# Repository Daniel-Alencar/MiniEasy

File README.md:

# Altímetro de dois eventos — classe EasyMini

Esquemático KiCad 10 de um altímetro barométrico de recuperação dupla (apogeu +
principal), equivalente em função ao Altus Metrum EasyMini: sensor barométrico,
registro de voo em flash, dois canais pirotécnicos com teste de continuidade,
download por USB. Sem GPS, sem acelerômetro, sem telemetria.

> **Defeito crítico em aberto:** `FIRE_B` está no PA9, que o bootloader da ROM
> leva a nível alto — o canal principal dispara se a placa entrar no bootloader
> (JP1 fechado ou flash vazia) com bateria e ignitor ligados. Até corrigir,
> grave firmware só com USB, sem bateria. Detalhes em [SINAIS.md](SINAIS.md).

Documentos:

- [SINAIS.md](SINAIS.md) — cada sinal: função, conexões, tensões, notas de firmware.
- [ALIMENTACAO.md](ALIMENTACAO.md) — por que o bloco de alimentação é assim: o "OU"
  de diodos, a escolha do regulador, o reservatório de disparo e o desacoplamento.

Arquivos:

| arquivo | conteúdo |
|---|---|
| `altimetro.kicad_sch` | esquemático, folha única A2, formato nativo KiCad 10 |
| `altimetro.kicad_pro` | projeto (inclui netclass `PIRO` de 1,0 mm) |
| `altimetro.kicad_pcb` | placa de 2 camadas, 66 × 26 mm, roteada |
| `altimetro.kicad_dru` | regra de DRC do USB que avança sobre a borda |
| `altimetro.pdf` | plotagem do esquemático |
| `fabricacao/` | Gerber + furação (zip), posição SMD, BOM, desenho de montagem, renders |
| `bom.csv` | lista de materiais exportada pelo KiCad, 54 componentes |
| `gerador/` | scripts que geram e verificam o esquemático |

## Arquitetura

```
J1 ──┬── C1 100µF ──────────────────► VBAT ──┬── J4 pino 1 (piro apogeu)
BAT  │   (reservatório de disparo)           └── J5 pino 1 (piro principal)
4-16V└── D1 ─┐
             ├─ VSYS ── U1 MCP1703 ── +3V3 ── MCU, baro, flash, buzzer
J3 USB ── D2 ┘         (SOT-89)
   └── U5 USBLC6 ── D+/D- ── U2 STM32F042K6T6 ──┬── SPI1 ──┬── U3 MS5607 (baro)
                                                │          └── U4 W25Q16 (flash)
                                                ├── ADC ───── continuidade A/B + VBAT
                                                ├── GPIO ──── Q1/Q2 AO3400A (disparo)
                                                └── TIM3 ──── Q3 + LS1 (buzzer)
```

Sete blocos no esquemático, numerados na folha: alimentação, MCU, barômetro +
memória, USB, canal A, canal B, aviso sonoro.

## Mapa de pinos do STM32F042K6T6 (LQFP32)

| pino | função | net | uso |
|---|---|---|---|
| 1, 5, 17 | VDD, VDDA, VDDIO2 | `+3V3` | C6/C9/C7 = 100 n, C8/C10 = 1 µF |
| 16, 32 | VSS, VSSA | `GND` | |
| 4 | NRST | `NRST` | C11 100 n + J2 pino 4 |
| 6 | PA0 / ADC_IN0 | `SNS_A` | continuidade canal apogeu |
| 7 | PA1 / ADC_IN1 | `SNS_B` | continuidade canal principal |
| 8 | PA2 / ADC_IN2 | `VB_SNS` | tensão de bateria (÷11) |
| 9 | PA3 | `CS_FLSH` | chip select da flash |
| 10 | PA4 | `CS_BARO` | chip select do barômetro |
| 11, 12, 13 | PA5/6/7 = SPI1 SCK/MISO/MOSI | `SCK` `MISO` `MOSI` | AF0 |
| 14 | PB0 / ADC_IN8 | `VU_SNS` | detecção de VBUS (÷2) |
| 15 | PB1 / TIM3_CH4 | `BEEP` | geração de tom |
| 18 | PA8 | `FIRE_A` | disparo apogeu |
| 19 | PA9 | `FIRE_B` | disparo principal |
| 21, 22 | PA11, PA12 | `USB_DM` `USB_DP` | USB FS device |
| 23, 24 | PA13, PA14 | `SWDIO` `SWCLK` | depuração |
| 25 | PA15 | `STAT` | LED de estado (dreno) |
| 31 | PB8 / BOOT0 | `BOOT0` | R3 10 k para GND + JP1 |
| 2, 3, 20, 26–30 | PF0, PF1, PA10, PB3–PB7 | — | marcados *no connect* |

Pinagens conferidas contra o datasheet: pino 17 é VDDIO2 e pino 16 é VSS (ST
STM32F042x4/x6); MS5607-02BA03 pino 4 = CSB e pino 5 = conexão interna, ambos no
mesmo net (datasheet TE, seção *Pin Configuration*). Atenção ao MCP1703: a
numeração muda com o encapsulamento — em SOT-89 é 1 = GND, 2 = VIN, 3 = VOUT
(em SOT-223 o pino 1 é VIN).

## Decisões de projeto

**STM32F042K6T6.** Mesma escolha do EasyMini v3. O que importa aqui é o USB
*crystal-less*: o periférico USB roda do HSI48 corrigido pelo CRS, sincronizado
ao SOF do host. Isso elimina cristal, dois capacitores e a área deles; PF0/PF1
ficam livres. Em troca, não há base de tempo precisa — o registro de voo usa o
HSI de ±1 % como base, suficiente para taxa de amostragem mas não para
medição de tempo absoluto.

**MS5607-02BA03 em SPI.** PS em GND seleciona SPI, compartilhando o barramento
com a flash. Resolução de 20 cm e conversão de 1 ms; limite de 1200 mbar e
10 mbar cobre do nível do mar a ~30 km. Barramento compartilhado é seguro porque
as duas conversões nunca são concorrentes: o firmware lê o barômetro e só depois
grava a amostra.

**W25Q16JV (16 Mbit).** 2 MByte dão ~44 min de registro a 100 Hz com amostra de
8 bytes (800 B/s) — de 10 a 20 voos de 2–4 min sem apagar; mais se a taxa cair
depois do apogeu. `WPn` e `HOLDn` ficam em nível alto por R4/R5 (10 k), o que
desativa a proteção de escrita por hardware e a pausa. Esses pinos não chegam ao
MCU, então a flash opera só em SPI simples.

**LDO MCP1703 em SOT-89, não SOT-23.** Com 16 V na entrada e 25 mA de consumo o
regulador dissipa (16 − 3,3) × 0,025 = 0,32 W. Em SOT-23 (θ_JA ≈ 250 °C/W) isso
são 80 °C de elevação; em SOT-89 (θ_JA ≈ 140 °C/W), 45 °C. O Iq de 2 µA importa
porque a placa fica armada na bancada por horas.

**OR de fontes por Schottky (D1/D2).** Bateria e USB alimentam o 3V3 por diodos
separados. O efeito colateral é a propriedade de segurança mais importante da
placa: `VBAT` alimenta os bornes pirotécnicos *diretamente*, não passa pelos
diodos — com só o USB conectado os canais ficam sem energia. Dá para programar e
baixar dados com os ignitores ligados.

**Disparo em lado baixo com pulldown no gate.** Q1/Q2 (AO3400A, 30 V, 5,7 A,
R_DS ≈ 30 mΩ) chaveiam o lado de GND do ignitor. R9/R13 de 100 k mantêm o gate
em GND enquanto o MCU está em reset, sem firmware ou travado — um pino em
tri-state não dispara nada. R8/R12 de 100 Ω limitam o pico de corrente de gate.

**Continuidade por divisor no dreno.** R10/R11 (100 k/10 k) medem o dreno de Q1.
Com ignitor intacto o nó fica em VBAT/11 (1,45 V em 16 V, 0,36 V em 4 V); com
ignitor aberto o divisor puxa o nó para 0 V. A corrente de teste que passa pelo
ignitor é VBAT/110 k, no máximo 145 µA — três ordens de grandeza abaixo da
corrente de não-disparo típica (250 mA) de um e-match. C16/C17 de 10 n filtram o
nó do ADC.

**C1 de 100 µF.** O disparo é um curto de ~1 Ω por ~1 s; sem reservatório local
a queda em VBAT faz o MCU resetar no pior momento possível. C1 fica no borne de
bateria, no mesmo laço de corrente dos bornes pirotécnicos.

**JP1 (BOOT0).** No STM32F042, BOOT0 é multiplexado com PB8. Fechando JP1 a
placa entra no bootloader DFU da ROM e aceita firmware pelo próprio USB, sem
programador. J2 (SWD 1×5, passo 1,27 mm) fica para depuração.

## Observações sobre o desenho

As ligações são feitas por **rótulos em stubs de 2,54 mm**: cada pino tem um fio
curto com o nome do net, em vez de fios longos atravessando a folha. É legal e
sem ambiguidade — a netlist extraída da geometria é idêntica à tabela de nets do
gerador — mas é um estilo compacto, não o traçado "bonito" de um esquemático
feito à mão. Reposicionar e traçar fios de verdade nos blocos é trabalho de
edição normal no Eeschema e não altera a netlist.

D1/D2/D3 estão desenhados com o catodo à esquerda (orientação padrão do símbolo,
sem espelhamento). Os rótulos deixam o sentido claro: em D1, `VBAT` entra pelo
anodo à direita e `VSYS` sai pelo catodo à esquerda.

## Placa

66 × 26 mm, 2 camadas, FR-4 1,6 mm, montagem SMD só no topo. Dois furos M3 nas
pontas, sem cobre (não ligam a placa ao suporte). Regras compatíveis com
fabricação padrão: trilha mínima 0,15 mm, folga 0,15 mm, via 0,6/0,3 mm.

| netclass | nets | trilha | folga |
|---|---|---|---|
| `PIRO` | `VBAT`, `PYRO_A`, `PYRO_B` | 0,8 mm | 0,3 mm |
| `POWER` | `+3V3`, `VSYS`, `VBUS`, `GND` | 0,4 mm | 0,2 mm |
| Default | sinais | 0,25 mm | 0,2 mm |

Disposição: bornes na borda inferior (entrada do fio para fora), USB na borda
superior esquerda, alimentação à esquerda, MCU no centro com os desacoplamentos
colados aos pinos, flash e barômetro em cima à direita (longe do regulador),
buzzer embaixo à direita. Plano de GND nas duas faces, costurado por vias.

Decisões de layout:

- **Bornes de 3,5 mm** (Metz Connect RT06302HBWC, 10 A, 0,14–1,5 mm²) em vez dos
  de 5,08 mm: metade da área, e mesma série de parafuso.
- **Pads SMD com ligação sólida ao plano**, alívio térmico só nos passantes.
  Importa para o GND do protetor de ESD (U5) e para a fonte de Q1/Q2, por onde
  volta a corrente de disparo. O pad de GND do header SWD também é sólido: no
  passo de 1,27 mm não cabem dois raios térmicos.
- **Faixa sem vias acima de cada borne** (área de regra) para os rótulos
  `+BAT-`, `APO`, `PRI` — furo de via corta a serigrafia.
- Referências que não cabem sem cobrir pad, via ou outra peça ficam fora da
  serigrafia e aparecem no desenho de montagem (`fabricacao/altimetro-montagem.pdf`).
  O verso traz legenda completa dos bornes e a pinagem do SWD.

### Gerar a placa

```sh
FREEROUTING=/caminho/freerouting-2.4.1.jar JAVA=/caminho/java25/bin/java gerador/fazer_pcb.sh
```

Requer KiCad 10 (módulo Python `pcbnew`), Java 25+ e Freerouting 2.4.1. O script
posiciona (conectores e CIs em posição fixa; passivos pelo lugar livre mais
perto do pino que atendem), exporta DSN com as larguras por classe, autorroteia,
cria planos e costura, posiciona a serigrafia e roda o DRC com paridade de
esquemático. **Só grava no projeto se o DRC passar sem nenhuma violação.** O
Freerouting não é determinístico: cada execução dá um traçado diferente, todos
verificados pelo mesmo DRC.

### Antes de encomendar

- Rodar o DRC no GUI e olhar a placa: o roteamento é automático. Funcional e
  verificado, mas vale revisar os laços de disparo e o USB a olho.
- Para montagem na JLCPCB/PCBWay: a BOM não tem códigos de fornecedor (LCSC), e
  o arquivo de posição usa a rotação do KiCad — alguns encapsulamentos (SOT-23,
  SOT-89) precisam de correção de rotação no visualizador do fabricante.
- O buzzer puxa ~100 mA de pico do 3V3 a 4 kHz. O firmware não deve tocá-lo
  enquanto mede pressão para referência de solo.

## Notas para o layout da PCB

1. O laço de disparo (J1 → C1 → J4/J5 → Q1/Q2 → GND) carrega alguns ampères por
   ~1 s. Netclass `PIRO` já está configurada em 1,0 mm; mantenha o laço curto e
   com área pequena, e não passe sinais de ADC por dentro dele.
2. O MS5607 precisa de abertura de ventilação para a pressão ambiente e **não
   pode ser lavado** (o datasheet é explícito: usar pasta no-clean). Mantenha a
   área reservada sob o sensor livre de trilhas, conforme o pad layout da TE.
3. Separe o GND de retorno pirotécnico do GND analógico do divisor de
   continuidade, unindo-os num único ponto junto ao borne de bateria.
4. U5 (USBLC6) vai o mais próximo possível do conector USB, antes de qualquer
   outra coisa nas linhas D+/D-.
5. Reserve lugar para fixar a bateria e os fios dos ignitores: são eles que
   sofrem a aceleração, não os componentes SMD.

## Verificação

`gerador/verificar.sh` gera o esquemático a partir das bibliotecas do KiCad
instalado e só grava o resultado se tudo passar:

1. o gerador recusa pino sem net e sem *no connect*, pino em dois nets, e dois
   símbolos de alimentação no mesmo ponto;
2. `check_sch.py` reextrai a netlist da geometria do arquivo e compara com a
   tabela `NETS`;
3. `check_layout.py` procura sobreposição de símbolos e rótulos e itens fora da
   folha;
4. `kicad-cli sch upgrade` converte para o formato nativo;
5. ERC do KiCad com todas as severidades — **0 erros, 0 avisos**;
6. `netcheck.py` compara a netlist exportada pelo próprio KiCad com a tabela
   `NETS` e confere cada footprint contra o filtro de footprint do símbolo;
7. exporta `altimetro.pdf` e `bom.csv`.

## O que não está feito

- Firmware e certificação.
- Proteção contra inversão de polaridade da bateria: D1 protege só o ramo de
  3V3. Os bornes pirotécnicos estão em `VBAT` direto, então bateria invertida
  polariza Q1/Q2 pelo diodo de corpo. Se isso preocupar, um P-FET em série na
  entrada resolve, ao custo de R_DS no caminho de disparo.
- Um elemento de armamento em série (chave física ou segundo FET) nos canais
  pirotécnicos. O EasyMini também não tem, mas é o acréscimo que eu faria antes
  de tratar a placa como produto.

## Regenerar

```sh
gerador/verificar.sh                      # usa /usr/share/kicad/symbols
gerador/verificar.sh /caminho/symbols     # outra instalação
```

A tabela `NETS` em `gerador/gen_sch.py` é a fonte da verdade das ligações: o
gerador falha se algum pino ficar sem net e sem *no connect*, se um pino aparecer
em dois nets, ou se dois símbolos de alimentação caírem no mesmo ponto. Depois de
editar o esquemático à mão no Eeschema, não regenere — o gerador sobrescreve o
posicionamento.

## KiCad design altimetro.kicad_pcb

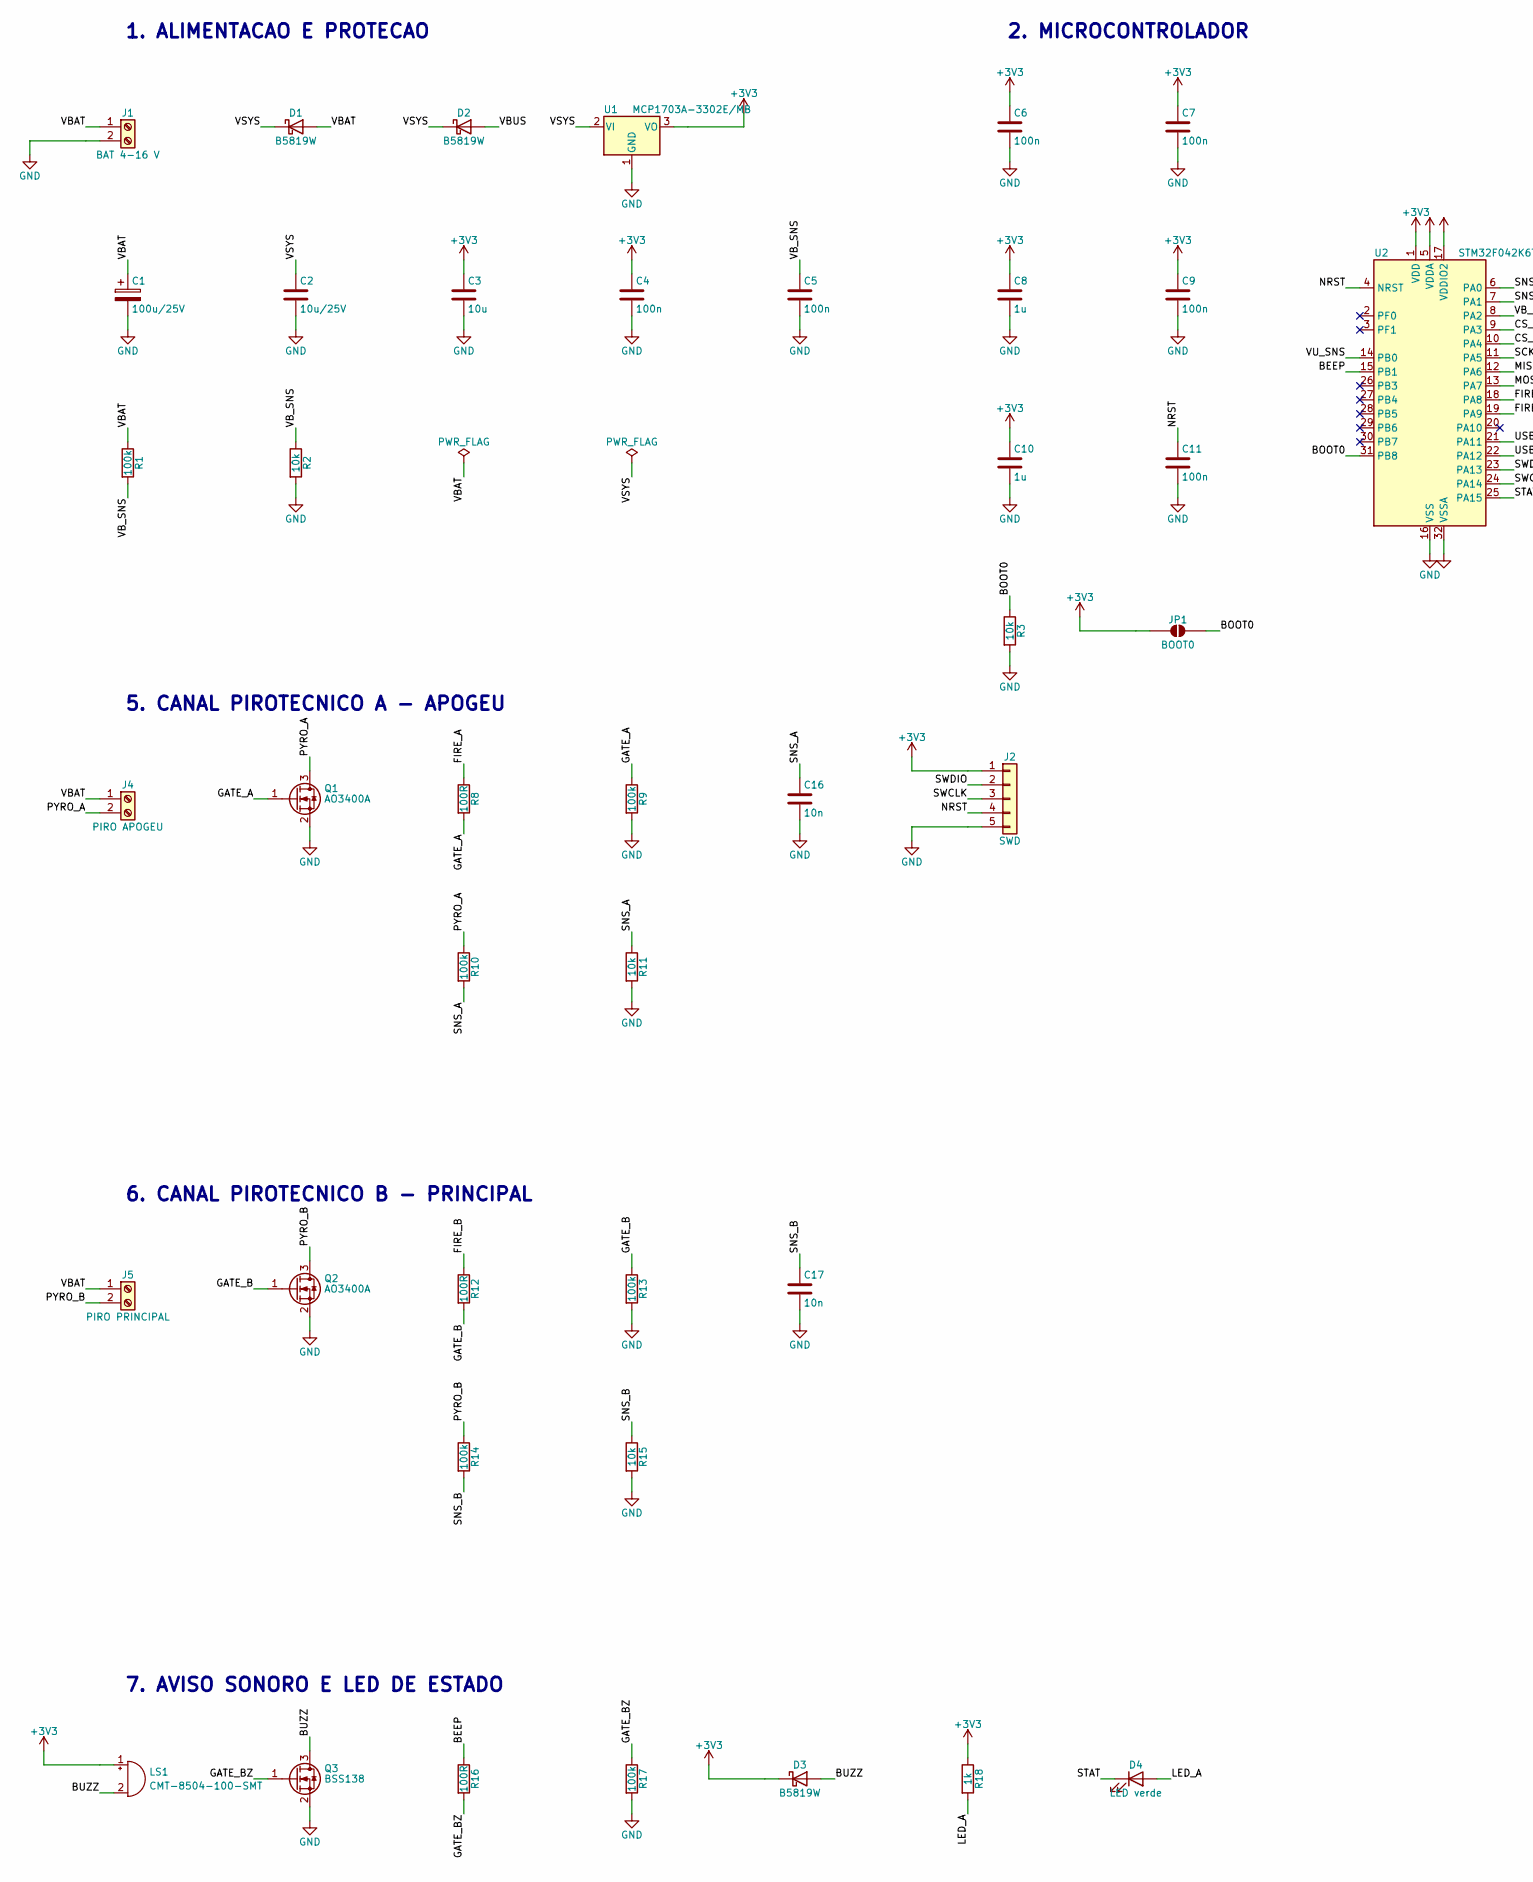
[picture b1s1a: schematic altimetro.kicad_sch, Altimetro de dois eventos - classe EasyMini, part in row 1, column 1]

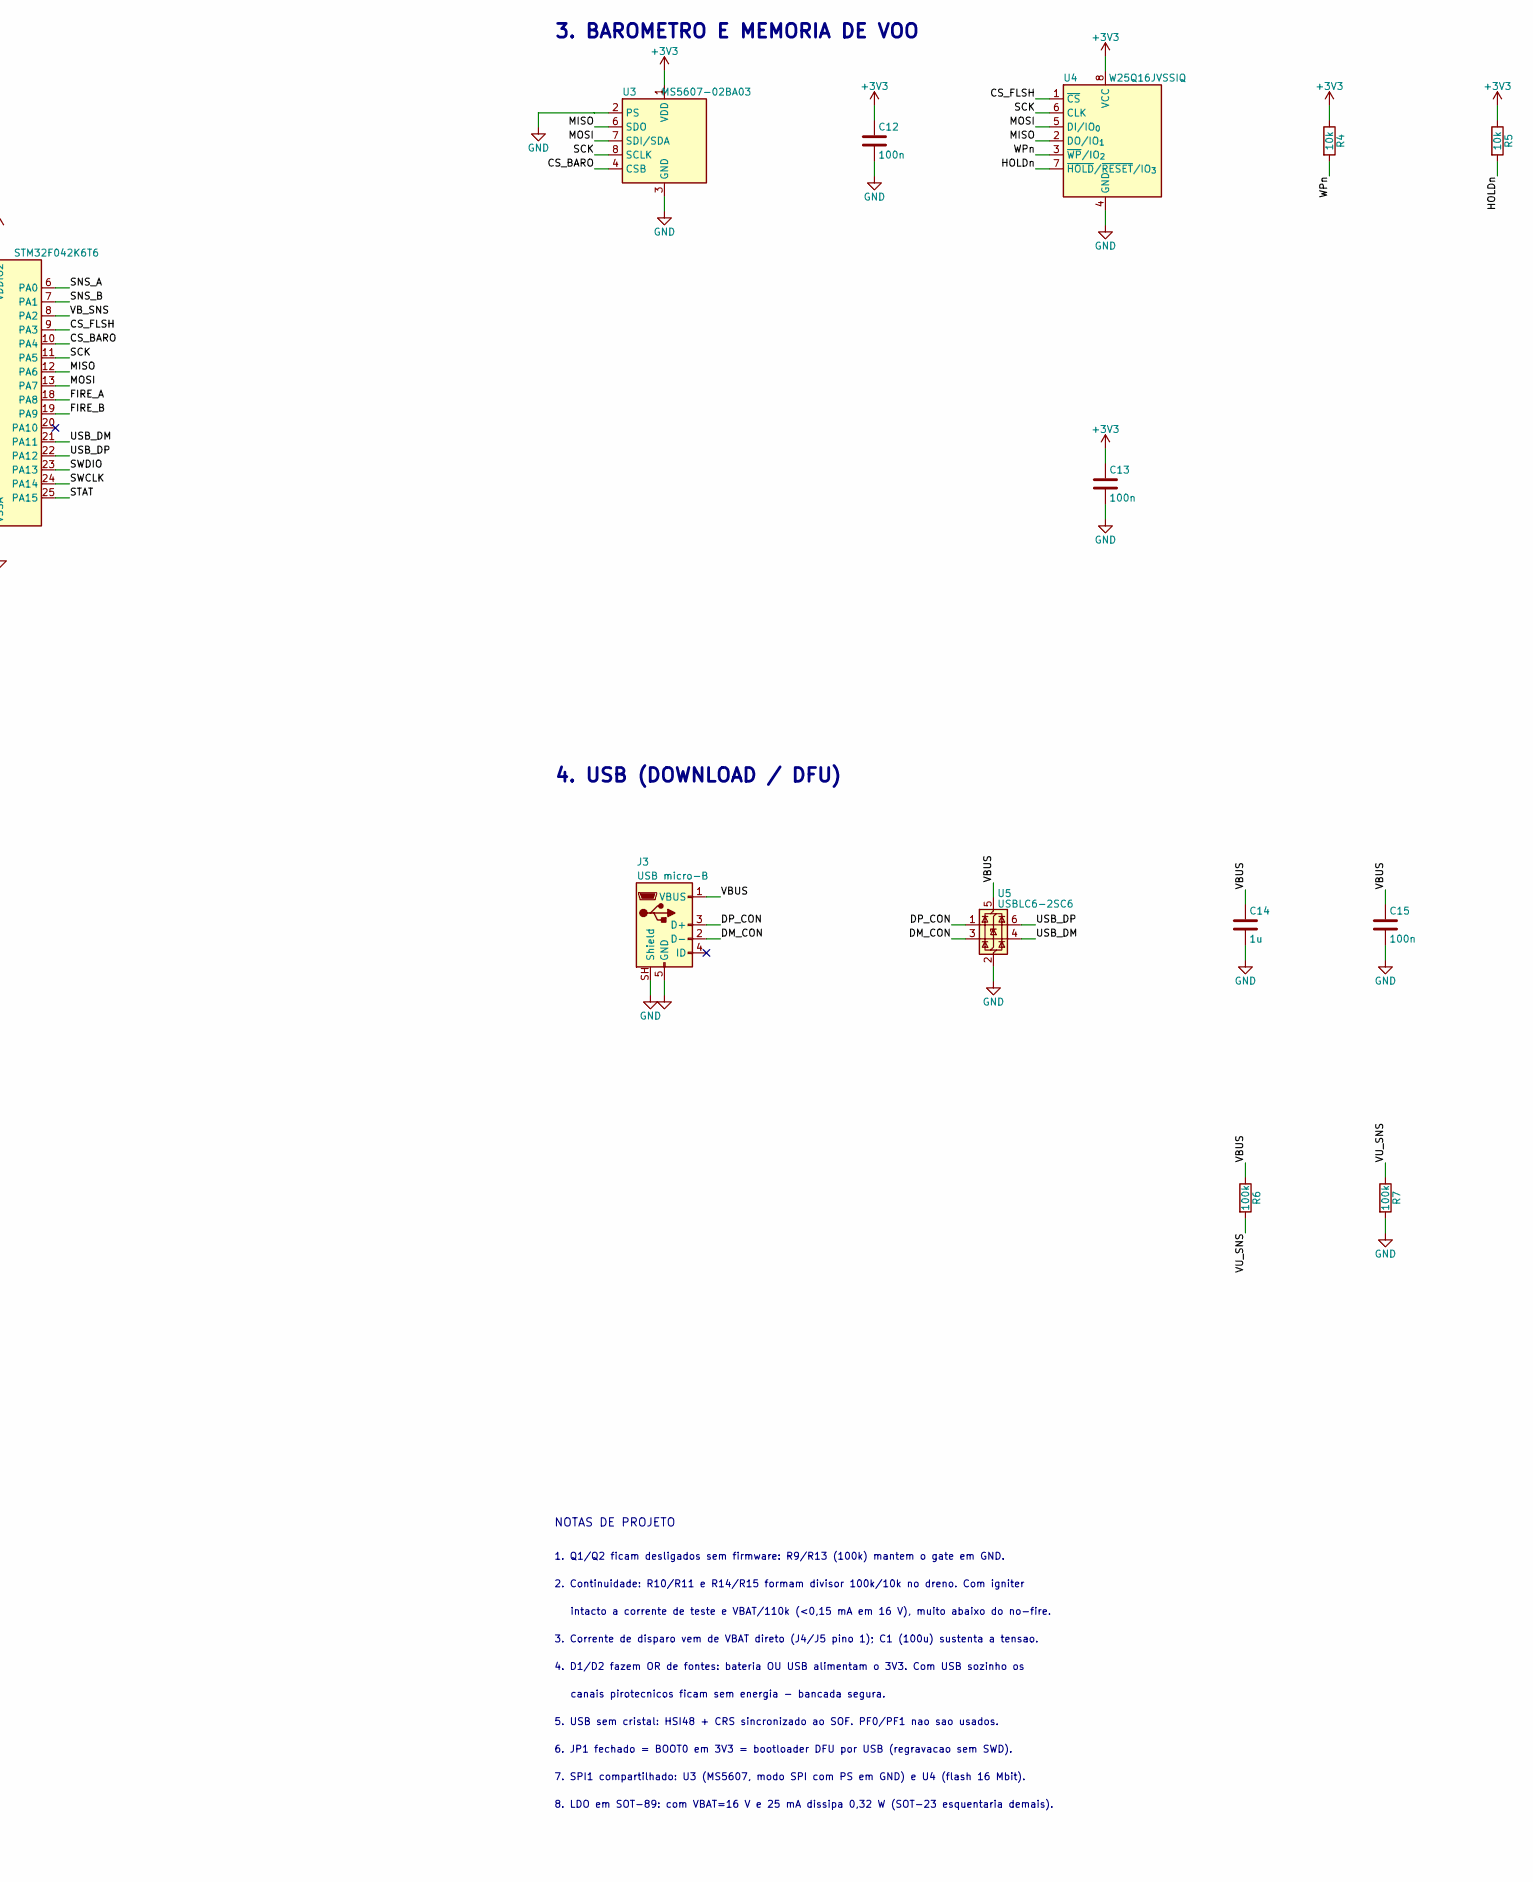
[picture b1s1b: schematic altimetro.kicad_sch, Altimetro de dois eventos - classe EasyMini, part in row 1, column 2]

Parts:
C1: 100u/25V; CP_Elec_6.3x7.7
C2: 10u/25V; C_0805_2012Metric
C3: 10u; C_0805_2012Metric
C4, C5, C6, C7, C9, C11, C12, C13, C15: 100n; C_0603_1608Metric
C8, C10, C14: 1u; C_0603_1608Metric
C16, C17: 10n; C_0603_1608Metric
D1, D2, D3: B5819W; D_SOD-123
D4: LED verde; LED_0603_1608Metric
J1: BAT 4-16 V; TerminalBlock_MetzConnect_Type059_RT06302HBWC_1x02_P3.50mm_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
J2: SWD; PinHeader_1x05_P1.27mm_Vertical
J3: USB micro-B; USB_Micro-B_Molex_47346-0001
J4: PIRO APOGEU; TerminalBlock_MetzConnect_Type059_RT06302HBWC_1x02_P3.50mm_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
J5: PIRO PRINCIPAL; TerminalBlock_MetzConnect_Type059_RT06302HBWC_1x02_P3.50mm_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
JP1: BOOT0; SolderJumper-2_P1.3mm_Open_RoundedPad1.0x1.5mm
LS1: CMT-8504-100-SMT; MagneticBuzzer_CUI_CMT-8504-100-SMT
Q1, Q2: AO3400A; SOT-23
Q3: BSS138; SOT-23
R1, R6, R7, R9, R10, R13, R14, R17: 100k; R_0603_1608Metric
R2, R3, R4, R5, R11, R15: 10k; R_0603_1608Metric
R8, R12, R16: 100R; R_0603_1608Metric
R18: 1k; R_0603_1608Metric
U1: MCP1703A-3302E/MB; SOT-89-3
U2: STM32F042K6T6; LQFP-32_7x7mm_P0.8mm
U3: MS5607-02BA03; LGA-8_3x5mm_P1.25mm
U4: W25Q16JVSSIQ; SOIC-8_5.3x5.3mm_P1.27mm
U5: USBLC6-2SC6; SOT-23-6

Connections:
+3V3: C3.1, C4.1, C6.1, C7.1, C8.1, C9.1, C10.1, C12.1, C13.1, D3.1 (K), J2.1, JP1.1 (A), LS1.1 (+), R4.1, R5.1, R18.1, U1.3 (VO), U2.1 (VDD), U2.5 (VDDA), U2.17 (VDDIO2), U3.1 (VDD), U4.8 (VCC)
/BEEP: R16.1, U2.15 (PB1)
/BOOT0: JP1.2 (B), R3.1, U2.31 (PB8)
/BUZZ: D3.2 (A), LS1.2 (-), Q3.3 (D)
/CS_BARO: U2.10 (PA4), U3.4 (CSB), U3.5 (CSB)
/CS_FLSH: U2.9 (PA3), U4.1 (~CS)
/DM_CON: J3.2 (D-), U5.3 (I/O2)
/DP_CON: J3.3 (D+), U5.1 (I/O1)
/FIRE_A: R8.1, U2.18 (PA8)
/FIRE_B: R12.1, U2.19 (PA9)
/GATE_A: Q1.1 (G), R8.2, R9.1
/GATE_B: Q2.1 (G), R12.2, R13.1
/GATE_BZ: Q3.1 (G), R16.2, R17.1
/HOLDn: R5.2, U4.7 (~HOLD/~RESET/IO_{3})
/LED_A: D4.2 (A), R18.2
/MISO: U2.12 (PA6), U3.6 (SDO), U4.2 (DO/IO_{1})
/MOSI: U2.13 (PA7), U3.7 (SDI/SDA), U4.5 (DI/IO_{0})
/NRST: C11.1, J2.4, U2.4 (NRST)
/PYRO_A: J4.2, Q1.3 (D), R10.1
/PYRO_B: J5.2, Q2.3 (D), R14.1
/SCK: U2.11 (PA5), U3.8 (SCLK), U4.6 (CLK)
/SNS_A: C16.1, R10.2, R11.1, U2.6 (PA0)
/SNS_B: C17.1, R14.2, R15.1, U2.7 (PA1)
/STAT: D4.1 (K), U2.25 (PA15)
/SWCLK: J2.3, U2.24 (PA14)
/SWDIO: J2.2, U2.23 (PA13)
/USB_DM: U2.21 (PA11), U5.4 (I/O2)
/USB_DP: U2.22 (PA12), U5.6 (I/O1)
/VBAT: C1.1, D1.2 (A), J1.1, J4.1, J5.1, R1.1
/VBUS: C14.1, C15.1, D2.2 (A), J3.1 (VBUS), R6.1, U5.5 (VBUS)
/VB_SNS: C5.1, R1.2, R2.1, U2.8 (PA2)
/VSYS: C2.1, D1.1 (K), D2.1 (K), U1.2 (VI)
/VU_SNS: R6.2, R7.1, U2.14 (PB0)
/WPn: R4.2, U4.3 (~WP/IO_{2})
GND: C1.2, C2.2, C3.2, C4.2, C5.2, C6.2, C7.2, C8.2, C9.2, C10.2, C11.2, C12.2, C13.2, C14.2, C15.2, C16.2, C17.2, J1.2, J2.5, J3.5 (GND), J3.SH (Shield), Q1.2 (S), Q2.2 (S), Q3.2 (S), R2.2, R3.2, R7.2, R9.2, R11.2, R13.2, R15.2, R17.2, U1.1 (GND), U2.16 (VSS), U2.32 (VSSA), U3.2 (PS), U3.3 (GND), U4.4 (GND), U5.2 (GND)

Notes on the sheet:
8. LDO em SOT-89: com VBAT=16 V e 25 mA dissipa 0,32 W (SOT-23 esquentaria demais).
4. D1/D2 fazem OR de fontes: bateria OU USB alimentam o 3V3. Com USB sozinho os
2. MICROCONTROLADOR
intacto a corrente de teste e VBAT/110k (<0,15 mA em 16 V), muito abaixo do no-fire.
3. BAROMETRO E MEMORIA DE VOO
1. Q1/Q2 ficam desligados sem firmware: R9/R13 (100k) mantem o gate em GND.
4. USB (DOWNLOAD / DFU)
7. SPI1 compartilhado: U3 (MS5607, modo SPI com PS em GND) e U4 (flash 16 Mbit).
6. JP1 fechado = BOOT0 em 3V3 = bootloader DFU por USB (regravacao sem SWD).
3. Corrente de disparo vem de VBAT direto (J4/J5 pino 1); C1 (100u) sustenta a tensao.
2. Continuidade: R10/R11 e R14/R15 formam divisor 100k/10k no dreno. Com igniter
NOTAS DE PROJETO
canais pirotecnicos ficam sem energia - bancada segura.
6. CANAL PIROTECNICO B - PRINCIPAL
5. USB sem cristal: HSI48 + CRS sincronizado ao SOF. PF0/PF1 nao sao usados.
7. AVISO SONORO E LED DE ESTADO
5. CANAL PIROTECNICO A - APOGEU
1. ALIMENTACAO E PROTECAO

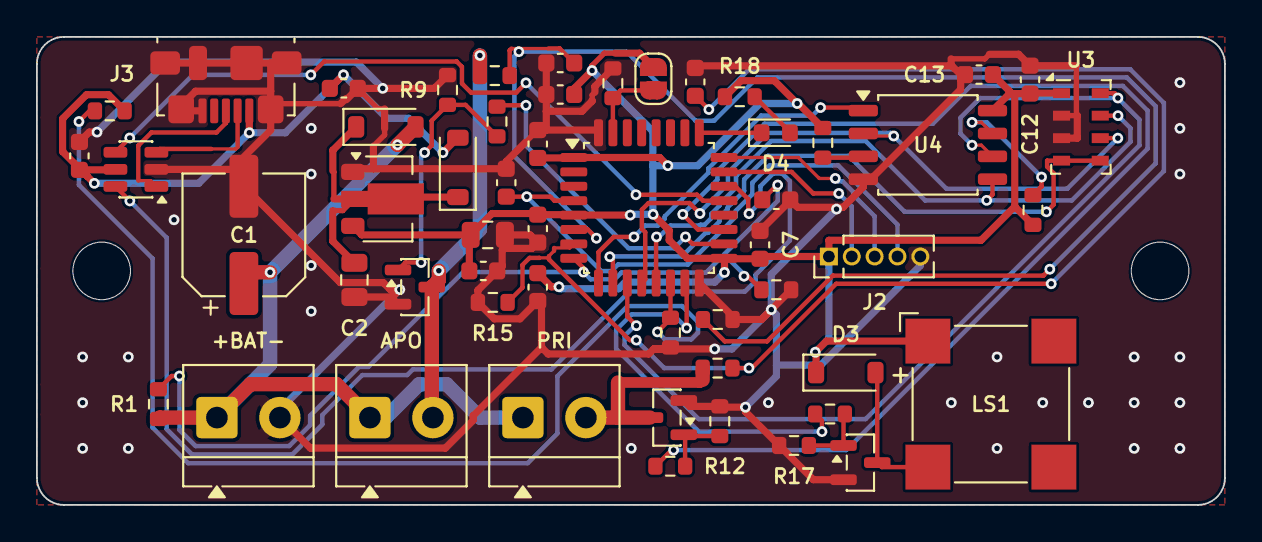
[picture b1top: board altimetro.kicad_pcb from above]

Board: 2 copper layers, 66.0 x 26.0 mm, 56 parts (0 on the bottom side), 35 nets.

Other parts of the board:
H1, H2: M3; MountingHole_3.2mm_M3

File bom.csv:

"Referencias","Valor","Footprint","Qtd"
"C1","100u/25V","Capacitor_SMD:CP_Elec_6.3x7.7","1"
"C2","10u/25V","Capacitor_SMD:C_0805_2012Metric","1"
"C3","10u","Capacitor_SMD:C_0805_2012Metric","1"
"C4,C5,C6,C7,C9,C11,C12,C13,C15","100n","Capacitor_SMD:C_0603_1608Metric","9"
"C8,C10,C14","1u","Capacitor_SMD:C_0603_1608Metric","3"
"C16,C17","10n","Capacitor_SMD:C_0603_1608Metric","2"
"D1,D2,D3","B5819W","Diode_SMD:D_SOD-123","3"
"D4","LED verde","LED_SMD:LED_0603_1608Metric","1"
"J1","BAT 4-16 V","TerminalBlock_MetzConnect:TerminalBlock_MetzConnect_Type059_RT06302HBWC_1x02_P3.50mm_Horizontal","1"
"J2","SWD","Connector_PinHeader_1.27mm:PinHeader_1x05_P1.27mm_Vertical","1"
"J3","USB micro-B","Connector_USB:USB_Micro-B_Molex_47346-0001","1"
"J4","PIRO APOGEU","TerminalBlock_MetzConnect:TerminalBlock_MetzConnect_Type059_RT06302HBWC_1x02_P3.50mm_Horizontal","1"
"J5","PIRO PRINCIPAL","TerminalBlock_MetzConnect:TerminalBlock_MetzConnect_Type059_RT06302HBWC_1x02_P3.50mm_Horizontal","1"
"LS1","CMT-8504-100-SMT","Buzzer_Beeper:MagneticBuzzer_CUI_CMT-8504-100-SMT","1"
"Q1,Q2","AO3400A","Package_TO_SOT_SMD:SOT-23","2"
"Q3","BSS138","Package_TO_SOT_SMD:SOT-23","1"
"R1,R6,R7,R9,R10,R13,R14,R17","100k","Resistor_SMD:R_0603_1608Metric","8"
"R2,R3,R4,R5,R11,R15","10k","Resistor_SMD:R_0603_1608Metric","6"
"R8,R12,R16","100R","Resistor_SMD:R_0603_1608Metric","3"
"R18","1k","Resistor_SMD:R_0603_1608Metric","1"
"U1","MCP1703A-3302E/MB","Package_TO_SOT_SMD:SOT-89-3","1"
"U2","STM32F042K6T6","Package_QFP:LQFP-32_7x7mm_P0.8mm","1"
"U3","MS5607-02BA03","Package_LGA:LGA-8_3x5mm_P1.25mm","1"
"U4","W25Q16JVSSIQ","Package_SO:SOIC-8_5.3x5.3mm_P1.27mm","1"
"U5","USBLC6-2SC6","Package_TO_SOT_SMD:SOT-23-6","1"
